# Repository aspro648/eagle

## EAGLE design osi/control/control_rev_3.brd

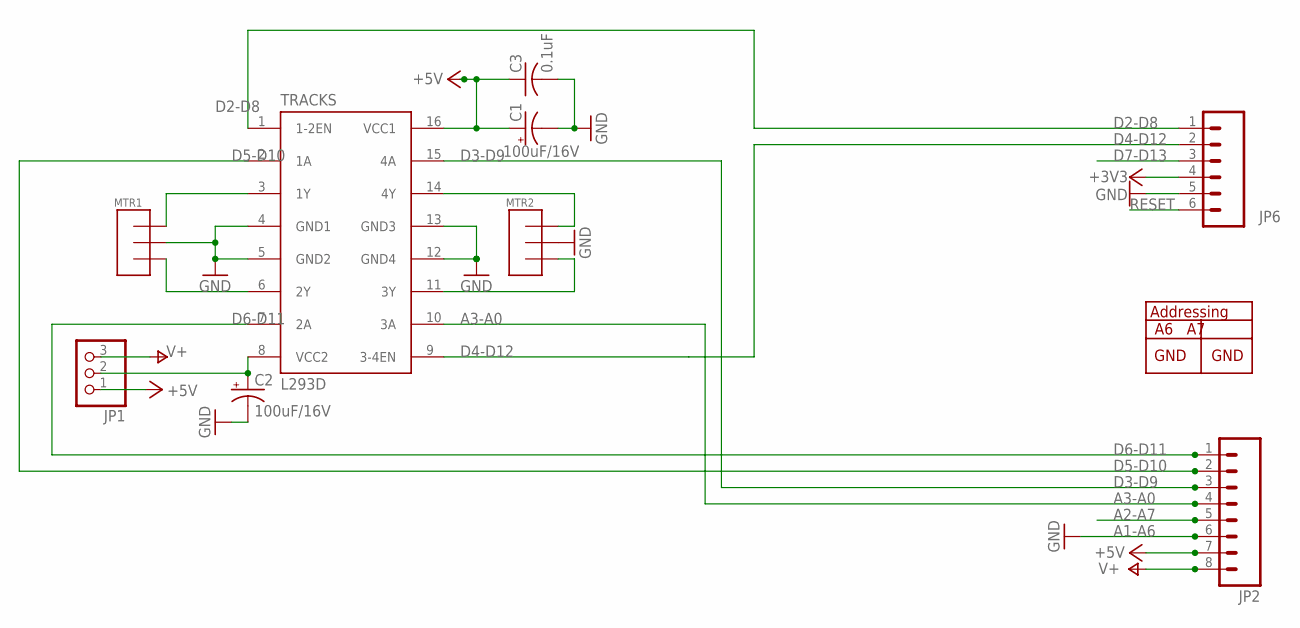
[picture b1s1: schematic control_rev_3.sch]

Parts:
C1, C2: 100uF/16V; E2,5-6
C3: 0.1uF; C025-025X050
JP1: PINHD-1X3; 1X03
JP2: M081X08; 1X08
JP6: M06SIP; 1X06
MTR1, MTR2: TERMINAL; TERMINAL_3
TRACKS: L293D; DIL16

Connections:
+3V3: JP6.4
+5V: C1.+, C3.1, JP1.1, JP2.7, TRACKS.16 (VCC1)
A1-A6: JP2.6
A2-A7: JP2.5
A3-A0: JP2.4, TRACKS.10 (3A)
D2-D8: JP6.1, TRACKS.1 (1-2EN)
D3-D9: JP2.3, TRACKS.15 (4A)
D4-D12: JP6.2, TRACKS.9 (3-4EN)
D5-D10: JP2.2, TRACKS.2 (1A)
D6-D11: JP2.1, TRACKS.7 (2A)
D7-D13: JP6.3
GND: C1.-, C2.-, C3.2, JP6.5, MTR1.P$2, MTR2.P$2, TRACKS.4 (GND1), TRACKS.5 (GND2), TRACKS.12 (GND4), TRACKS.13 (GND3)
unnamed: MTR1.P$1, TRACKS.3 (1Y)
unnamed: MTR2.P$1, TRACKS.14 (4Y)
unnamed: MTR1.P$3, TRACKS.6 (2Y)
unnamed: MTR2.P$3, TRACKS.11 (3Y)
unnamed: C2.+, JP1.2, TRACKS.8 (VCC2)
RESET: JP6.6
V+: JP1.3, JP2.8

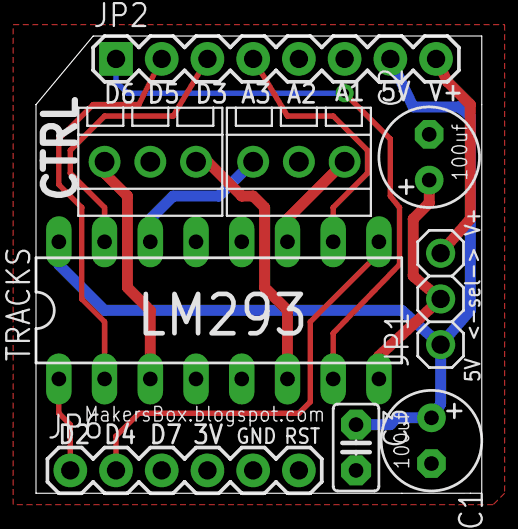
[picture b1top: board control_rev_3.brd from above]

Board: 2 copper layers, 24.8 x 25.4 mm, 9 parts (0 on the bottom side), 14 nets.

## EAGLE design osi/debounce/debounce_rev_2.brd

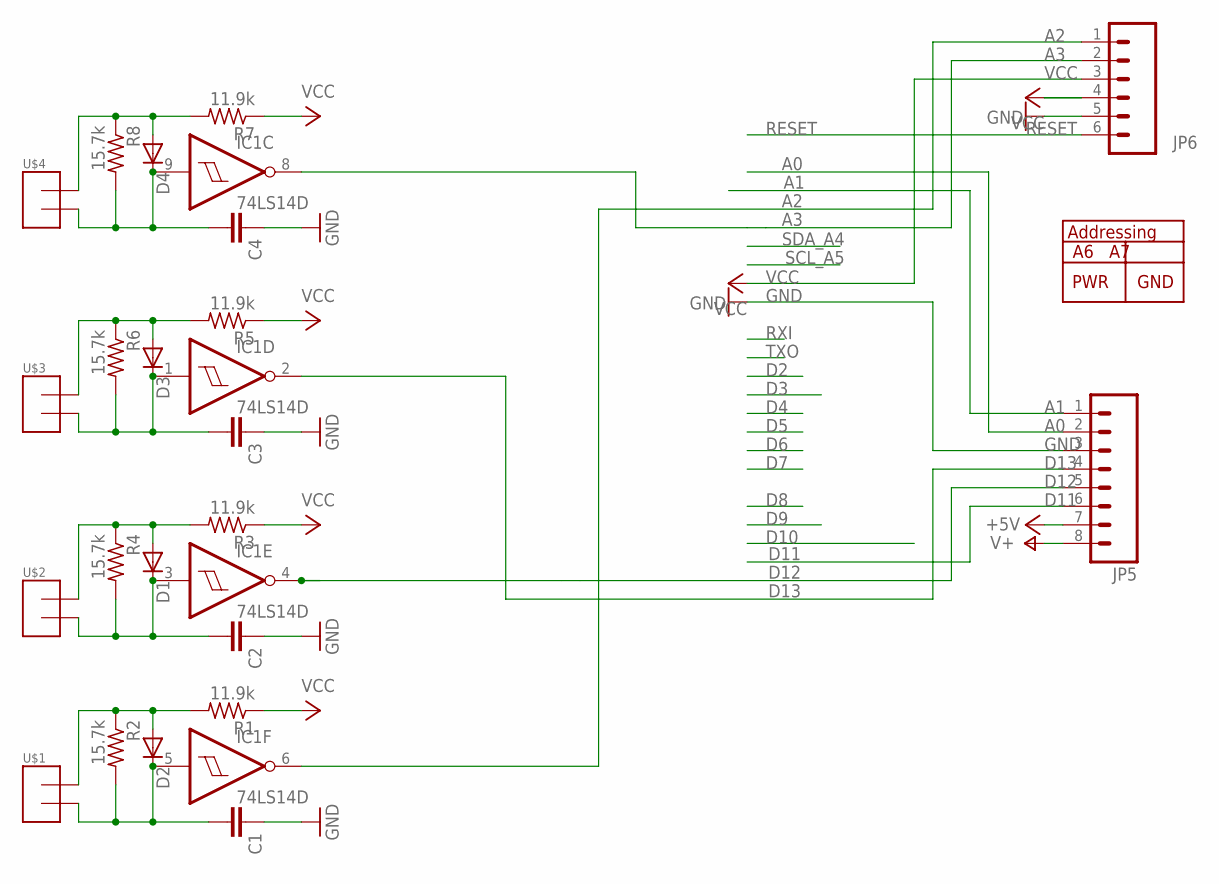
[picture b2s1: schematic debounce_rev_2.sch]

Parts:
C1, C2, C3, C4: CAPPTH; CAP-PTH-SMALL
D1, D2, D3, D4: DIODE-D-2.5; D-2.5
IC1: 74LS14D; SO14
JP5: M081X08; 1X08
JP6: M06SIP; 1X06
R1, R3, R5, R7: 11.9k; 0204V
R2, R4, R6, R8: 15.7k; 0204V
U$1, U$2, U$3, U$4: TERMINAL2; TERMINAL_2

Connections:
+5V: JP5.7
A0: JP5.2
A1: JP5.1
A2: IC1.6 (O), JP6.1
A3: IC1.8 (O), JP6.2
D11: JP5.6
D12: IC1.4 (O), JP5.5
D13: IC1.2 (O), JP5.4
GND: C1.1, C2.1, C3.1, C4.1, IC1.7 (GND), JP5.3, JP6.5
unnamed: D1.A, R3.2, R4.1, U$2.P$1
unnamed: C2.2, D1.C, IC1.3 (I), R4.2, U$2.P$2
unnamed: D2.A, R1.2, R2.1, U$1.P$1
unnamed: C1.2, D2.C, IC1.5 (I), R2.2, U$1.P$2
unnamed: D3.A, R5.2, R6.1, U$3.P$1
unnamed: C3.2, D3.C, IC1.1 (I), R6.2, U$3.P$2
unnamed: D4.A, R7.2, R8.1, U$4.P$1
unnamed: C4.2, D4.C, IC1.9 (I), R8.2, U$4.P$2
RESET: JP6.6
V+: JP5.8
VCC: IC1.14 (VCC), JP6.3, JP6.4, R1.1, R3.1, R5.1, R7.1

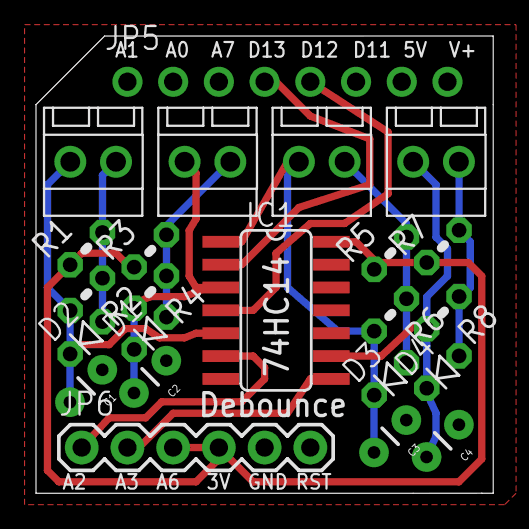
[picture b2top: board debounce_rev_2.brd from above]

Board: 2 copper layers, 25.4 x 25.4 mm, 23 parts (0 on the bottom side), 14 nets.

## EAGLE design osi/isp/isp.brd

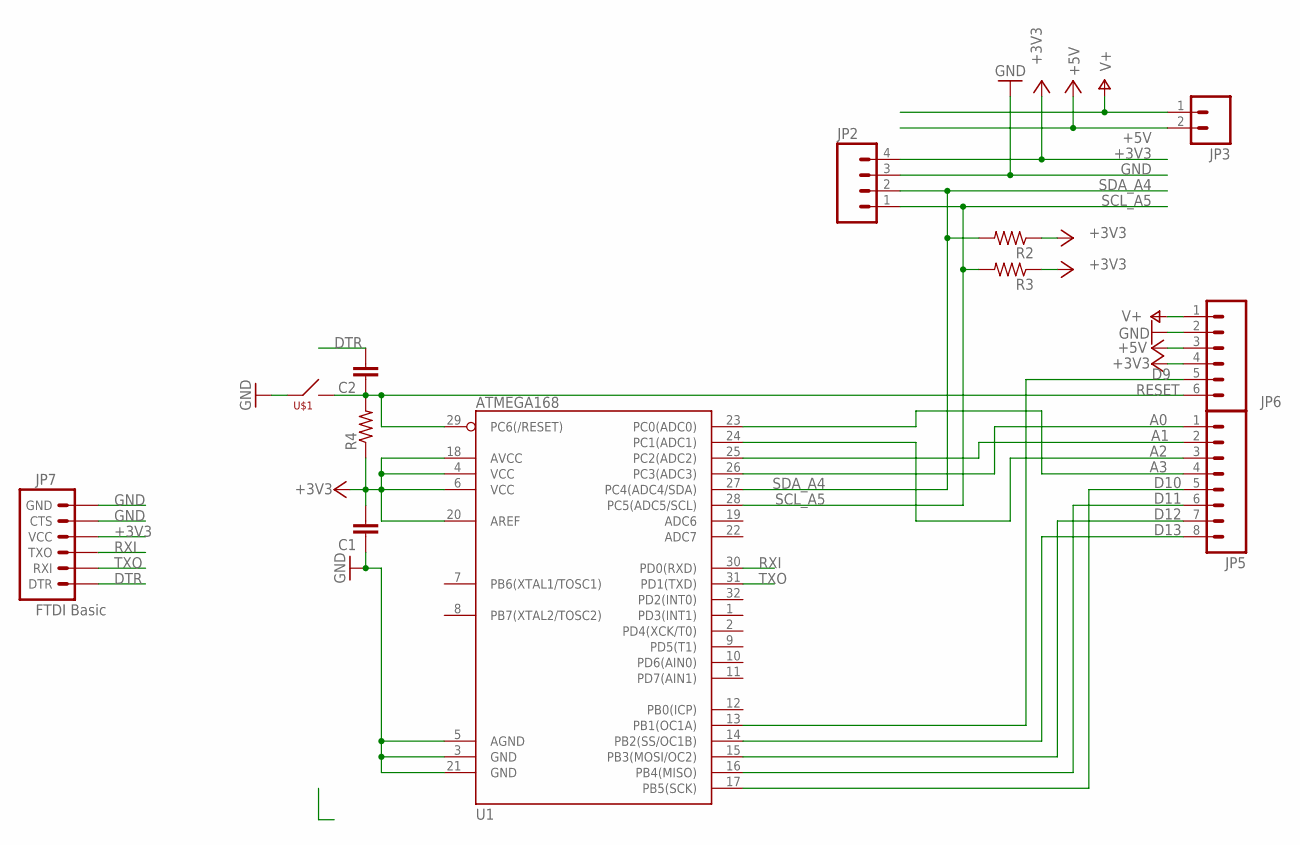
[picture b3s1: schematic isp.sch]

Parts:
C1, C2: CAPKIT; CAP-PTH-SMALL-KIT
JP2: M04PTH; 1X04
JP3: M02PTH; 1X02
JP5: M081X08; 1X08
JP6: M06SIP; 1X06
JP7: FTDI Basic; 1X06
R2, R3, R4: R-US_0204/2V; 0204V
U1: ATMEGA168; TQFP32-08
U$1: PTS635_SWITCH

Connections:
+3V3: C1.2, JP2.4, JP6.4, JP7.4 (VCC), R2.1, R3.1, R4.1, U1.4 (VCC), U1.6 (VCC), U1.18 (AVCC), U1.20 (AREF)
+5V: JP3.2, JP6.3
A0: JP5.4, U1.23 (PC0(ADC0))
A1: JP5.3, U1.24 (PC1(ADC1))
A2: JP5.2, U1.25 (PC2(ADC2))
A3: JP5.1, U1.26 (PC3(ADC3))
D9: JP6.5, U1.13 (PB1(OC1A))
D10: JP5.8, U1.14 (PB2(SS/OC1B))
D11: JP5.7, U1.15 (PB3(MOSI/OC2))
D12: JP5.6, U1.16 (PB4(MISO))
D13: JP5.5, U1.17 (PB5(SCK))
DTR: C2.2, JP7.1 (DTR)
GND: C1.1, JP2.3, JP6.2, JP7.5 (CTS), JP7.6 (GND), U1.3 (GND), U1.5 (AGND), U1.21 (GND), U$1.P$1
RESET: C2.1, JP6.6, R4.2, U1.29 (PC6(/RESET)), U$1.P$2
RXI: JP7.3 (TXO), U1.30 (PD0(RXD))
SCL_A5: JP2.1, R3.2, U1.28 (PC5(ADC5/SCL))
SDA_A4: JP2.2, R2.2, U1.27 (PC4(ADC4/SDA))
TXO: JP7.2 (RXI), U1.31 (PD1(TXD))
V+: JP3.1, JP6.1

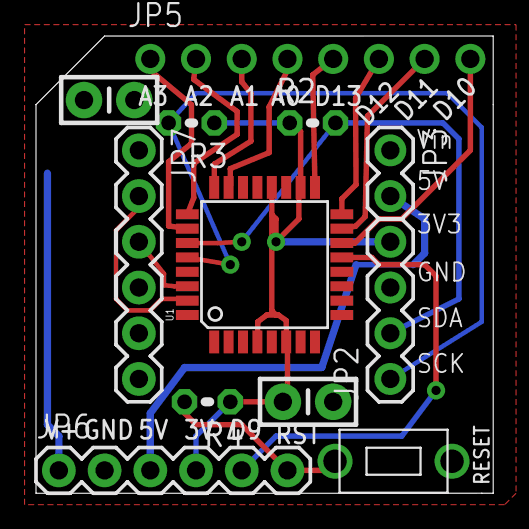
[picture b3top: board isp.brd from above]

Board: 2 copper layers, 25.4 x 25.4 mm, 12 parts (0 on the bottom side), 19 nets.

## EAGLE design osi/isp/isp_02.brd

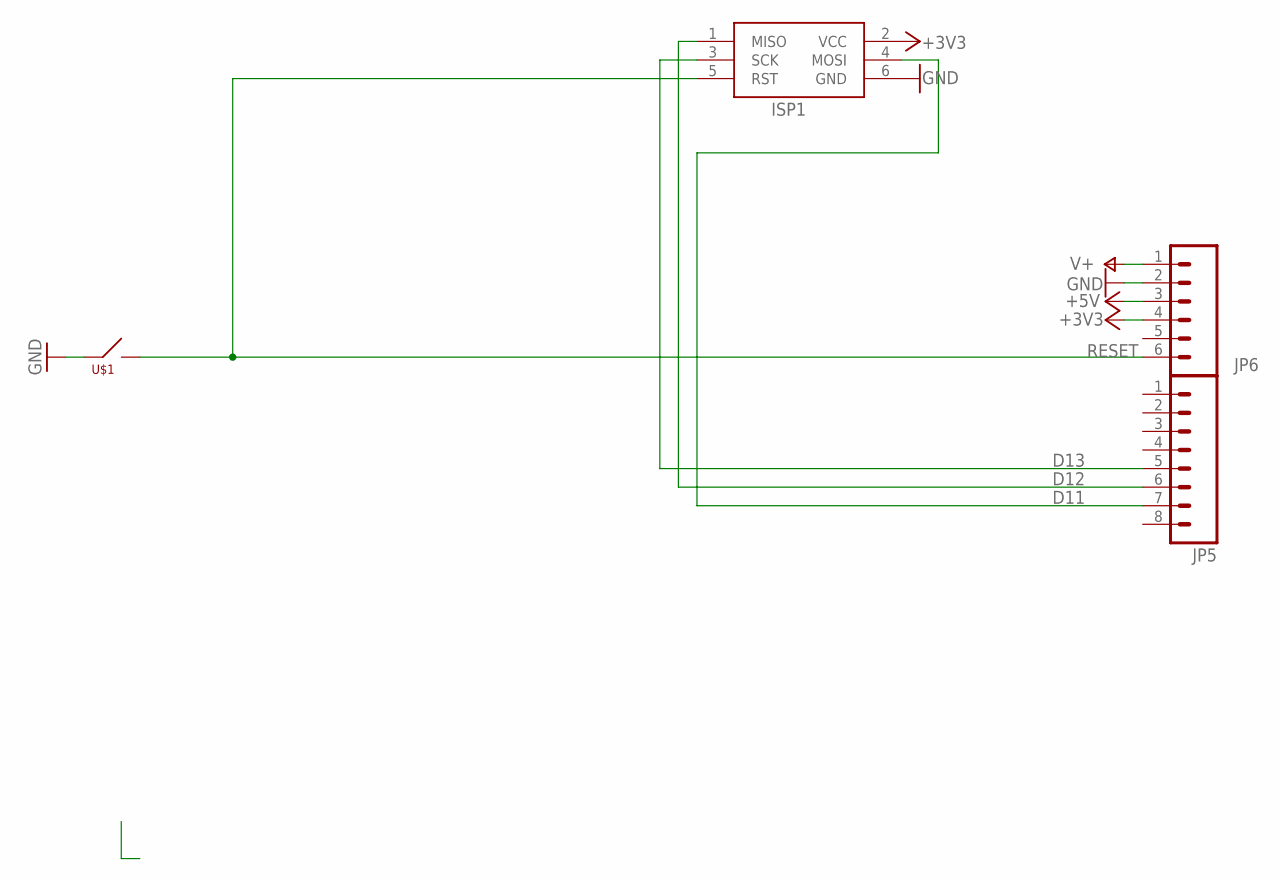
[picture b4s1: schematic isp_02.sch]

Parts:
ISP1: AVRISP-6; AVRISP
JP5: M081X08; 1X08
JP6: M06SIP; 1X06
U$1: PTS635_SWITCH

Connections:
+3V3: ISP1.2 (VCC), JP6.4
+5V: JP6.3
D11: ISP1.4 (MOSI), JP5.7
D12: ISP1.1 (MISO), JP5.6
D13: ISP1.3 (SCK), JP5.5
GND: ISP1.6 (GND), JP6.2, U$1.P$1
RESET: ISP1.5 (RST), JP6.6, U$1.P$2
V+: JP6.1

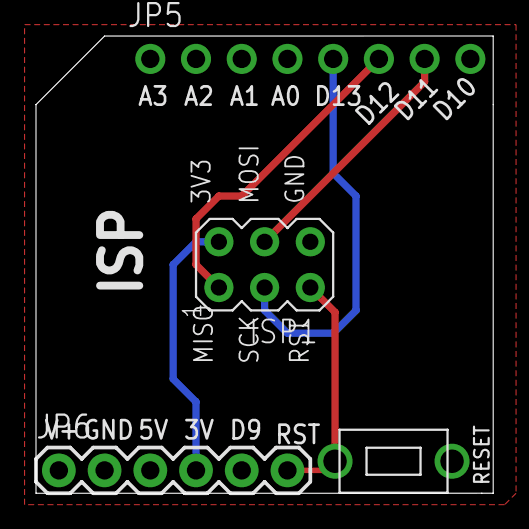
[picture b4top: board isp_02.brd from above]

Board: 2 copper layers, 25.4 x 25.4 mm, 4 parts (0 on the bottom side), 6 nets.

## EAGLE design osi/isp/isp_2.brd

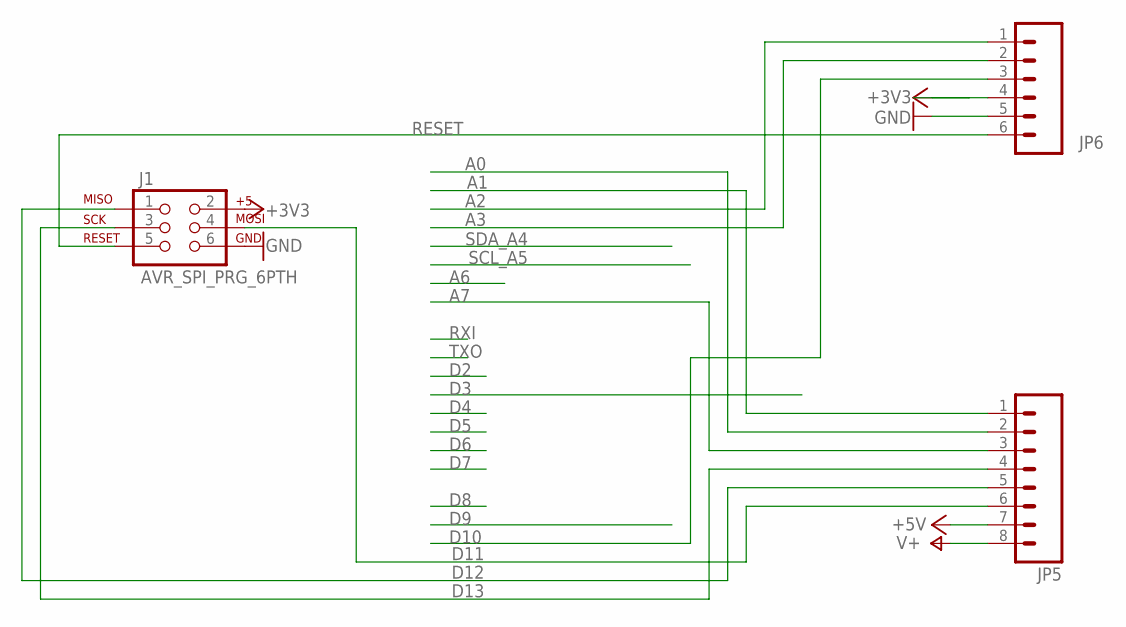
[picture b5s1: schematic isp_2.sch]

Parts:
J1: AVR_SPI_PRG_6PTH; 2X3
JP5: M081X08; 1X08
JP6: M06SIP; 1X06

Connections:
+3V3: J1.2, JP6.4
+5V: JP5.7
A0: JP5.2
A1: JP5.1
A2: JP6.1
A3: JP6.2
A7: JP5.3
D10: JP6.3
D11: J1.4, JP5.6
D12: J1.1, JP5.5
D13: J1.3, JP5.4
GND: J1.6, JP6.5
RESET: J1.5, JP6.6
V+: JP5.8

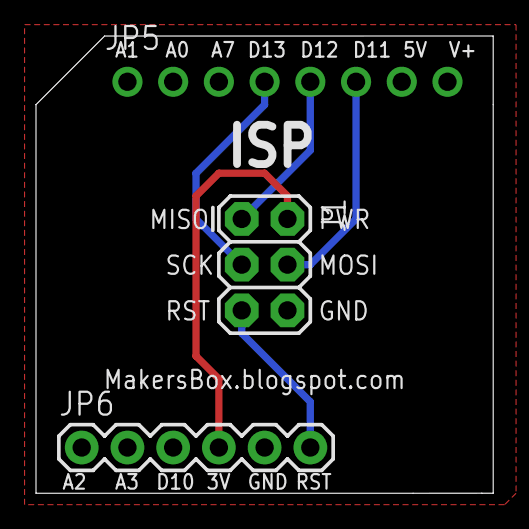
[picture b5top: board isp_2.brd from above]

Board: 2 copper layers, 25.4 x 25.4 mm, 3 parts (0 on the bottom side), 6 nets.

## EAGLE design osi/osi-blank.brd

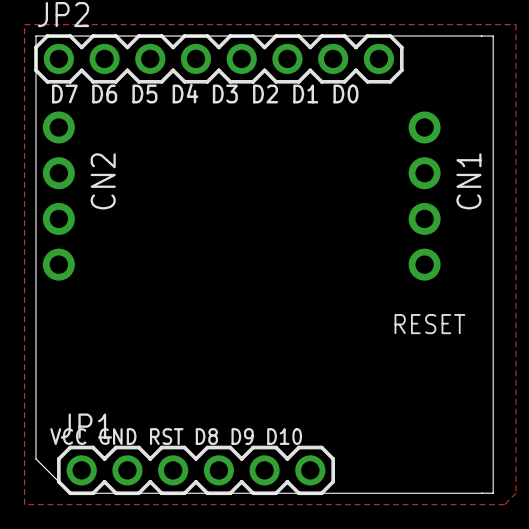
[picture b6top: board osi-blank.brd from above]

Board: 2 copper layers, 25.4 x 25.4 mm, 4 parts (0 on the bottom side), 4 nets, no tracks yet.

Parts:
CN1, CN2: 1X4-CLEANBIG; 1X04-CLEANBIG
JP1: 1X06
JP2: 1X08

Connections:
GND: CN1.2, CN2.2, JP1.2
SCK: CN1.4, CN2.4, JP2.2
SDA: CN1.3, CN2.3, JP2.4
VCC: CN1.1, CN2.1, JP1.1

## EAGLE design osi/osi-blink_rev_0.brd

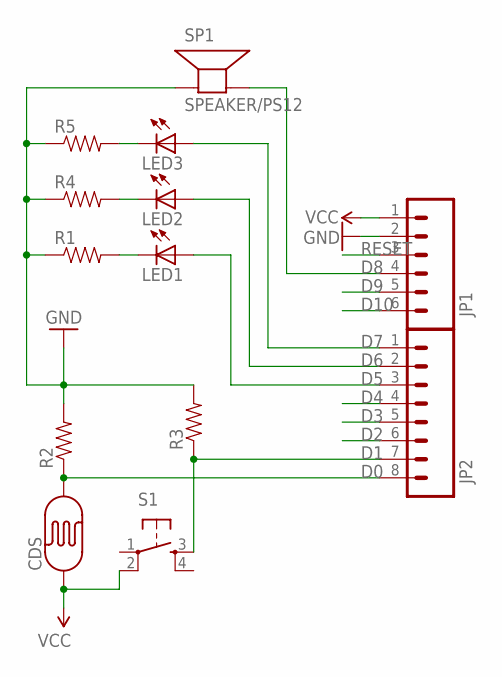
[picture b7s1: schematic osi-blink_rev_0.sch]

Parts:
CDS: PHOTOCELLPTH-KIT; PHOTOCELL-KIT
JP1: M06SIP; 1X06
JP2: M081X08; 1X08
LED1, LED2, LED3: LED3MM
R1, R2, R3, R4, R5: RESISTORKIT; AXIAL-0.3-KIT
S1: TAC_SWITCHPTH; TACTILE-PTH
SP1: SPEAKER/PS12; PS12

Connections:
D0: CDS.2, JP2.8, R2.P$1 (1)
D1: JP2.7, R3.P$1 (1), S1.3
D2: JP2.6
D3: JP2.5
D4: JP2.4
D5: JP2.3, LED1.A
D6: JP2.2, LED2.A
D7: JP2.1, LED3.A
D8: JP1.4, SP1.P$2 (-)
D9: JP1.5
D10: JP1.6
GND: JP1.2, R1.P$1 (1), R2.P$2 (2), R3.P$2 (2), R4.P$1 (1), R5.P$1 (1), SP1.P$1 (+)
unnamed: LED1.K (C), R1.P$2 (2)
unnamed: LED2.K (C), R4.P$2 (2)
unnamed: LED3.K (C), R5.P$2 (2)
RESET: JP1.3
VCC: CDS.1, JP1.1, S1.2

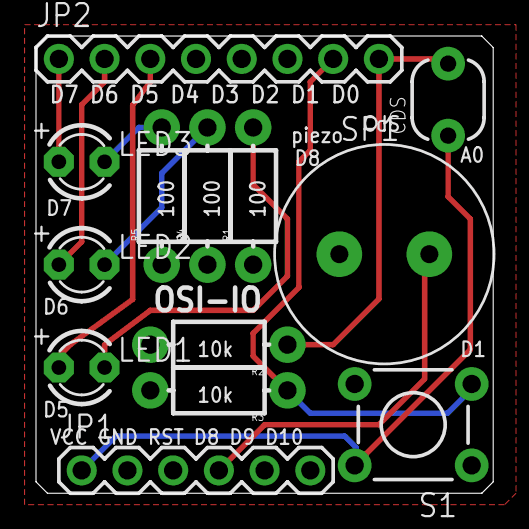
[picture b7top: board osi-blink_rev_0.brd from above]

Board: 2 copper layers, 25.4 x 25.4 mm, 13 parts (0 on the bottom side), 11 nets.

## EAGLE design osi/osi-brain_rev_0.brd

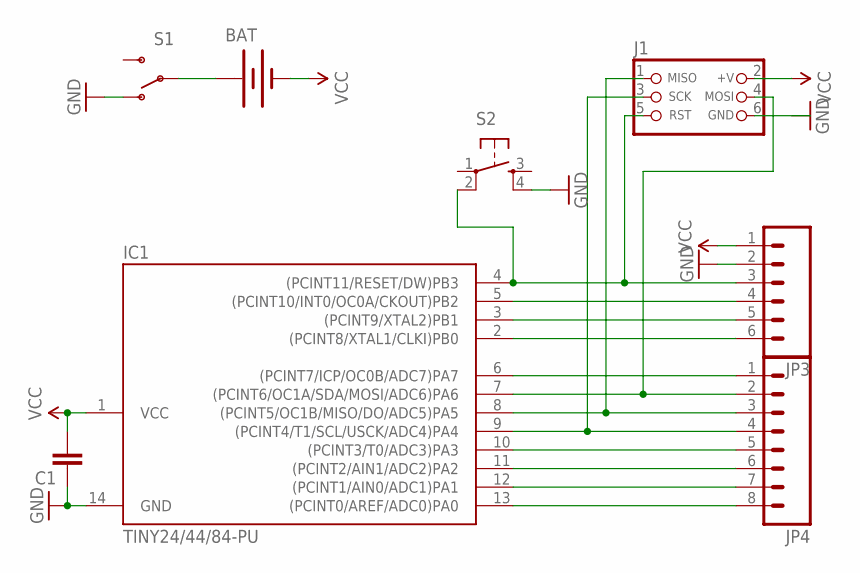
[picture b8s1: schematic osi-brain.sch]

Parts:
BAT: BATTERY20PTH; BATTCOM_20MM_PTH
C1: CAPKIT; CAP-PTH-SMALL-KIT
IC1: TINY24/44/84-PU; DIL14
J1: CON_HEADER_PRG_AVR_ICSP-PTH; HEADER_PRG_2X03
JP3: M06SIP; 1X06
JP4: M081X08; 1X08
S1: SWITCH-SPSTPTH; SWITCH-SPDT
S2: TAC_SWITCHPTH; TACTILE-PTH

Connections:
D0: IC1.13 ((PCINT0/AREF/ADC0)PA0), JP4.8
D1: IC1.12 ((PCINT1/AIN0/ADC1)PA1), JP4.7
D2: IC1.11 ((PCINT2/AIN1/ADC2)PA2), JP4.6
D3: IC1.10 ((PCINT3/T0/ADC3)PA3), JP4.5
D4: IC1.9 ((PCINT4/T1/SCL/USCK/ADC4)PA4), J1.3 (SCK), JP4.4
D5: IC1.8 ((PCINT5/OC1B/MISO/DO/ADC5)PA5), J1.1 (MISO), JP4.3
D6: IC1.7 ((PCINT6/OC1A/SDA/MOSI/ADC6)PA6), J1.4 (MOSI), JP4.2
D7: IC1.6 ((PCINT7/ICP/OC0B/ADC7)PA7), JP4.1
D8: IC1.5 ((PCINT10/INT0/OC0A/CKOUT)PB2), JP3.4
D9: IC1.3 ((PCINT9/XTAL2)PB1), JP3.5
D10: IC1.2 ((PCINT8/XTAL1/CLKI)PB0), JP3.6
GND: C1.1, IC1.14 (GND), JP3.2, S1.1 (O), S2.4
unnamed: BAT.1 (+), S1.2
RESET: IC1.4 ((PCINT11/RESET/DW)PB3), J1.5 (RST), JP3.3, S2.2
VCC: BAT.2 (-), C1.2, IC1.1 (VCC), J1.2 (+V), JP3.1

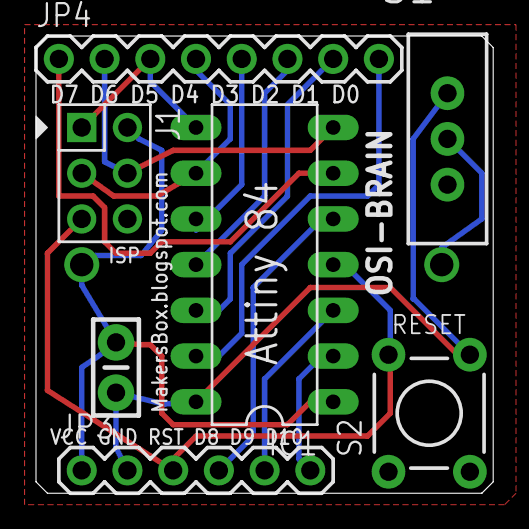
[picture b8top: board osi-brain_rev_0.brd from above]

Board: 2 copper layers, 25.4 x 25.4 mm, 8 parts (0 on the bottom side), 15 nets.

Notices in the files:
parts and their libraries:
SparkFun: Licensing: CC v3.0 Share-Alike You are welcome to use this library for commercial purposes.
